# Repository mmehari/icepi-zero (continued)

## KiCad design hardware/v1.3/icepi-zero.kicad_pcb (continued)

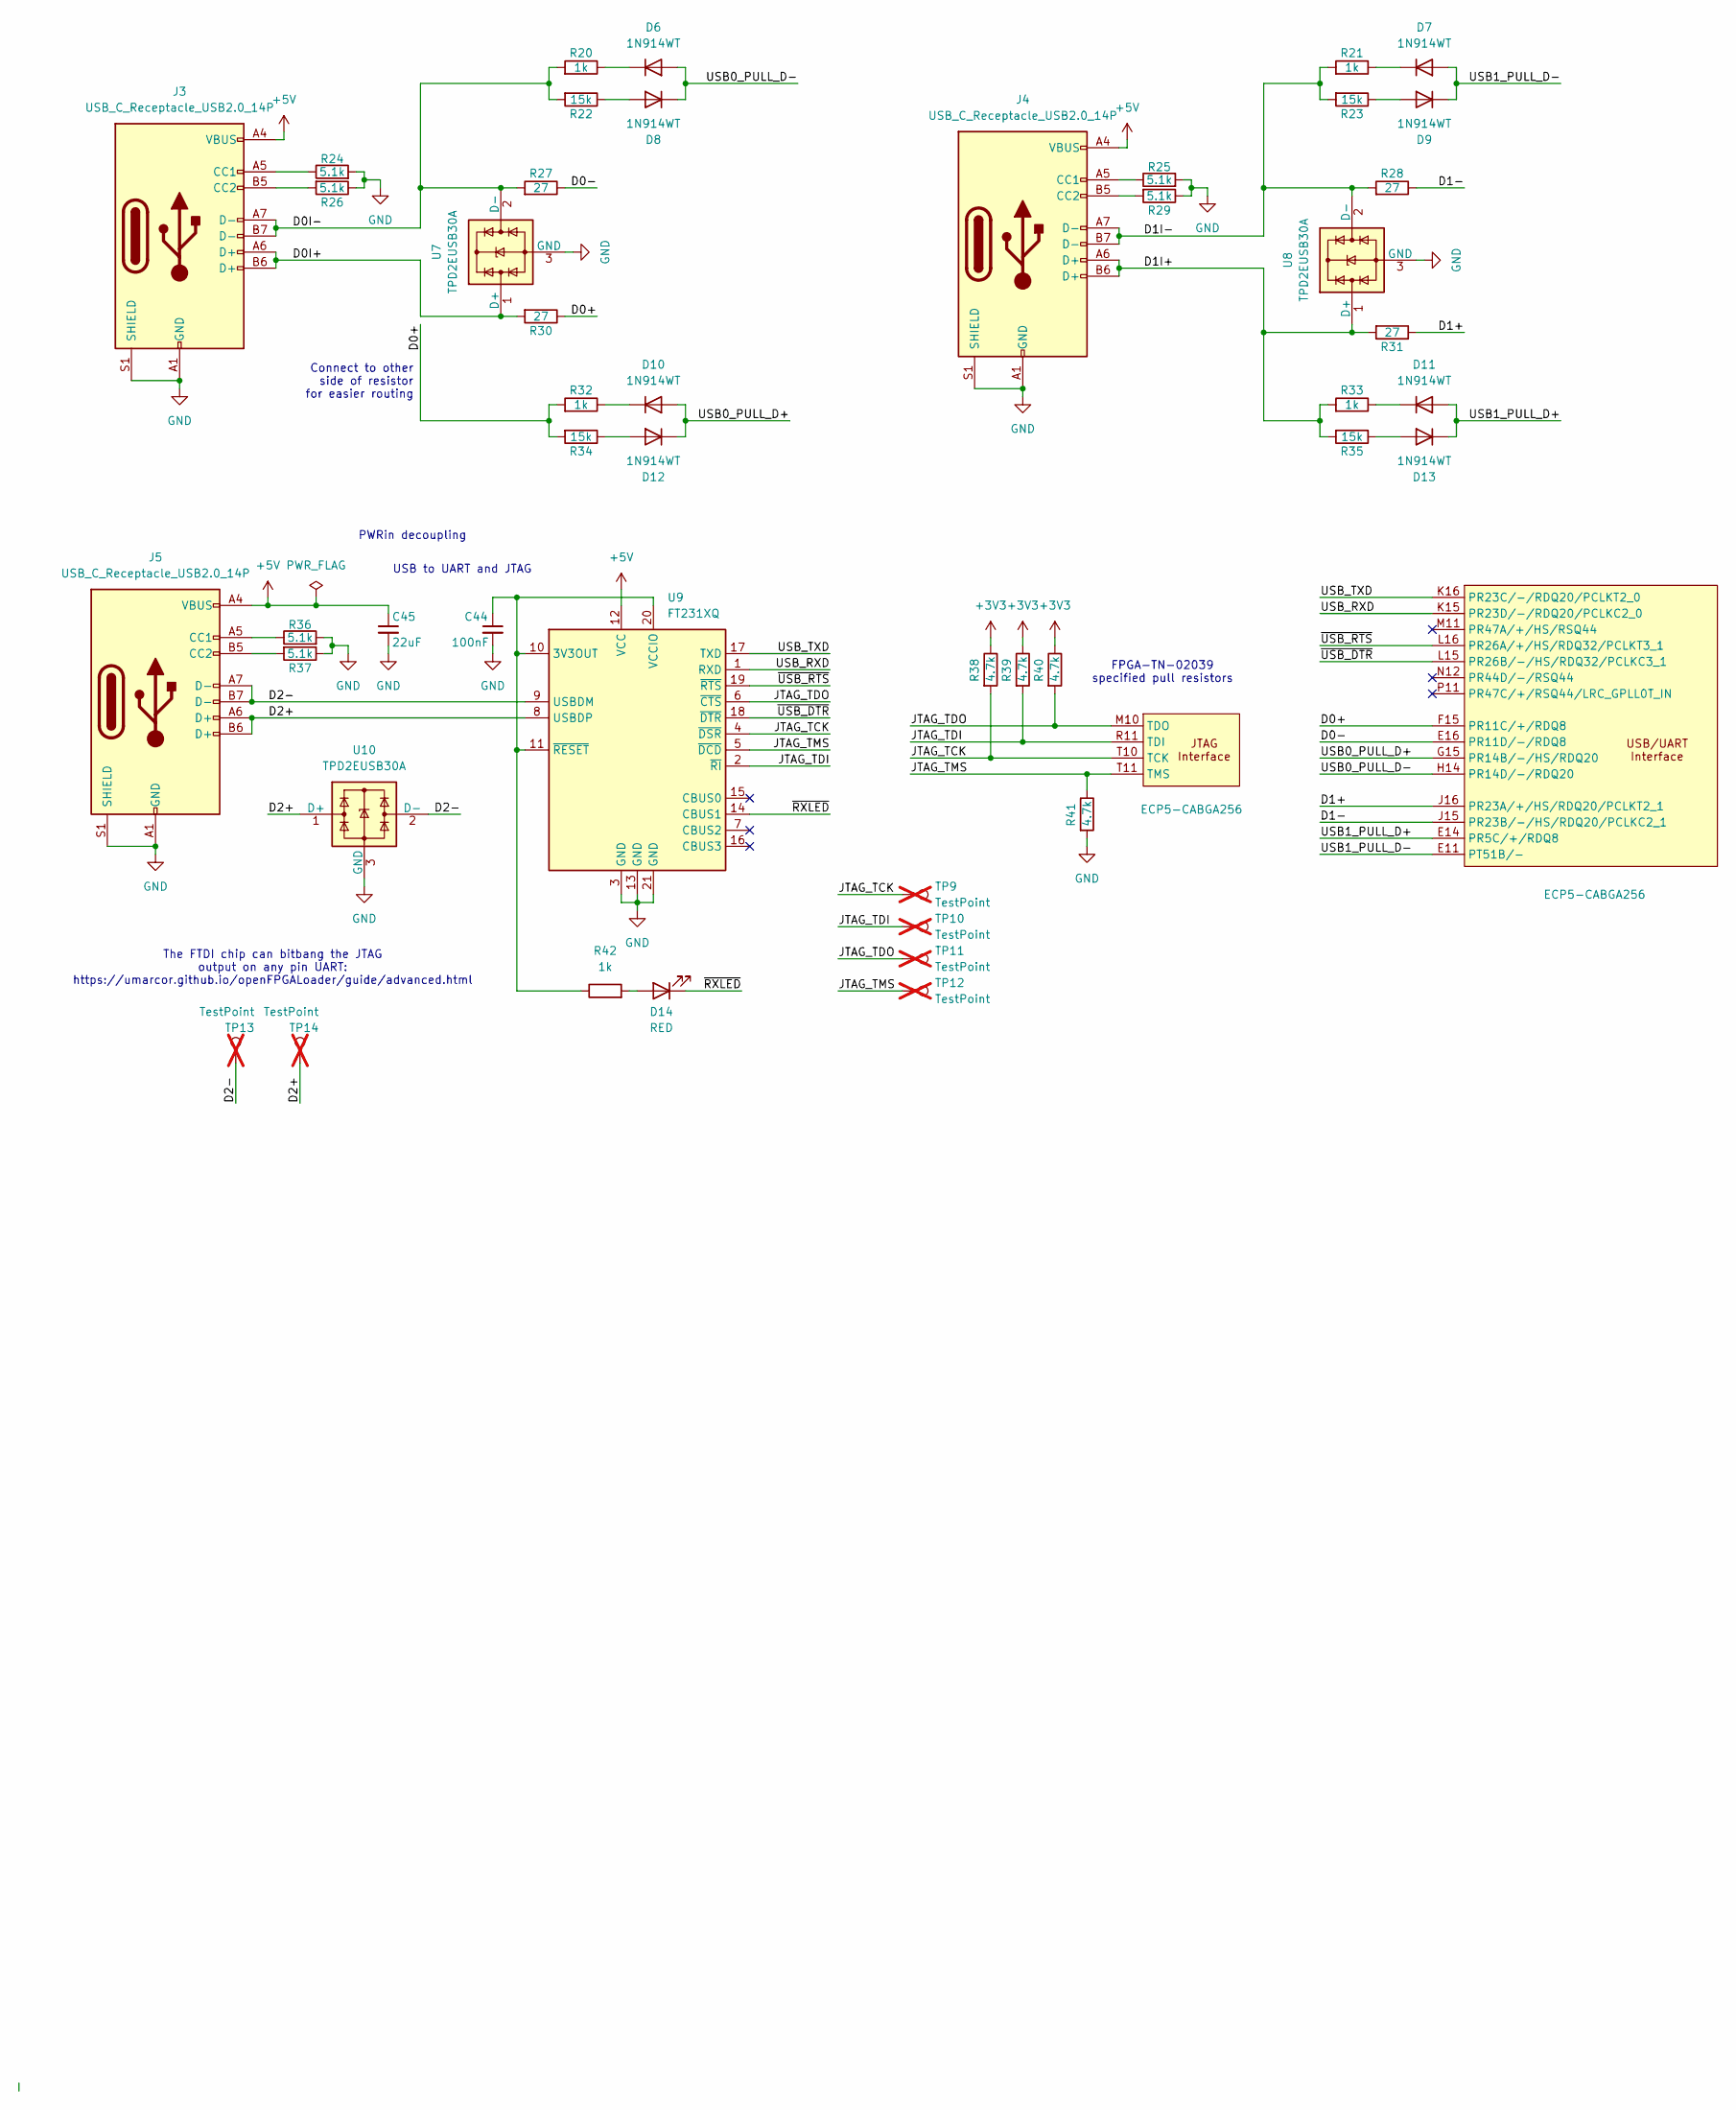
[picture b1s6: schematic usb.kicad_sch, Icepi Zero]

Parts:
C44: 100nF; C_0402_1005Metric; Manufactuer Part Number CL05B104KB54PNC; LCSC Part # C307331
C45: 22uF; C_0603_1608Metric; Manufactuer Part Number CL10A226MQ8NRNC; LCSC Part # C59461
D6, D7, D8, D9, D10, D11, D12, D13: 1N914WT; D_SOD-523; Manufactuer Part Number 1N914WT; LCSC Part # C2836064
D14: RED; LED_0603_1608Metric; Manufactuer Part Number KT-0603R; LCSC Part # C2286
J3, J4, J5: USB_C_Receptacle_USB2.0_14P; USB_C_Receptacle_GCT_USB4105-xx-A_16P_TopMnt_Horizontal; Manufactuer Part Number TYPE-C 16PIN 2MD(073); LCSC Part # C2765186
R20, R21, R32, R33, R42: 1k; R_0402_1005Metric; Manufactuer Part Number 0402WGF1001TCE; LCSC Part # C11702
R22, R23, R34, R35: 15k; R_0402_1005Metric; Manufactuer Part Number 0402WGF1502TCE; LCSC Part # C25756
R24, R25, R26, R29, R36, R37: 5.1k; R_0402_1005Metric; Manufactuer Part Number 0402WGF5101TCE; LCSC Part # C25905
R27, R28, R30, R31: 27; R_0201_0603Metric; Manufactuer Part Number 0201WMF270JTEE; LCSC Part # C473051
R38, R39, R40, R41: 4.7k; R_0402_1005Metric; Manufactuer Part Number 0402WGF4701TCE; LCSC Part # C25900
TP9, TP10, TP11, TP12: TestPoint; TestPoint_Pad_D1.0mm_Blank; not fitted
TP13, TP14: TestPoint; TestPoint_Pad_D2.0mm_Blank; not fitted
U1: ECP5-CABGA256; BGA-256_14.0x14.0mm_Layout16x16_P0.8mm_Ball0.45mm_Pad0.32mm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; Manufactuer Part Number LFE5U-25F-6BG256C; LCSC Part # C1521614
U7, U8, U10: TPD2EUSB30A; Texas_DRT-3; Manufactuer Part Number TPD2EUSB30ADRTR; LCSC Part # C3011197
U9: FT231XQ; QFN-20-1EP_4x4mm_P0.5mm_EP2.5x2.5mm; Manufactuer Part Number FT231XQ-R; LCSC Part # C132159

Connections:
+3V3: R38.1, R39.1, R40.1; also elsewhere on the board
+5V: C45.1, J3.A4 (VBUS), J3.A9 (VBUS), J3.B4 (VBUS), J3.B9 (VBUS), J4.A4 (VBUS), J4.A9 (VBUS), J4.B4 (VBUS), J4.B9 (VBUS), J5.A4 (VBUS), J5.A9 (VBUS), J5.B4 (VBUS), J5.B9 (VBUS), U9.12 (VCC); also elsewhere on the board
/DBG1: U1.C7 (PT27A/+/PCLKT0_1); also elsewhere on the board
/DBG2: U1.C8 (PT35A/+/PCLKT1_0); also elsewhere on the board
/GLOBAL_CLK: U1.M1 (PL26C/+/LDQ32/PCLKT6_0); also elsewhere on the board
/GPIO0: U1.G3 (PL14C/+/LDQ20/VREF1_7); also elsewhere on the board
/GPIO1: U1.K3 (PL20D/-/LDQS20); also elsewhere on the board
/GPIO2: U1.T2 (PL38D/-/LDQ44); also elsewhere on the board
/GPIO3: U1.R2 (PL38C/+/LDQ44); also elsewhere on the board
/GPIO4: U1.R1 (PL35B/-/HS/LDQ32/VREF1_6); also elsewhere on the board
/GPIO5: U1.E1 (PL11D/-/LDQ8); also elsewhere on the board
/GPIO6: U1.F3 (PL5D/-/LDQ8); also elsewhere on the board
/GPIO7: U1.G1 (PL20A/+/HS/LDQS20/GR_PCLK7_1); also elsewhere on the board
/GPIO8: U1.H2 (PL20C/+/LDQS20/GR_PCLK7_0); also elsewhere on the board
/GPIO9: U1.J1 (PL23A/+/HS/LDQ20/PCLKT7); also elsewhere on the board
/GPIO10: U1.L2 (PL26B/-/HS/LDQ32/PCLKC6_1); also elsewhere on the board
/GPIO11: U1.G2 (PL14B/-/HS/LDQ20); also elsewhere on the board
/GPIO12: U1.J3 (PL20B/-/HS/LDQSN20); also elsewhere on the board
/GPIO13: U1.E3 (PL5C/+/LDQ8); also elsewhere on the board
/GPIO14: U1.P1 (PL35A/+/HS/LDQ32); also elsewhere on the board
/GPIO15: U1.N1 (PL32A/+/HS/LDQS32); also elsewhere on the board
/GPIO16: U1.H3 (PL14D/-/lDQ20); also elsewhere on the board
/GPIO17: U1.R3 (PL41B/-/HS/LDQ44); also elsewhere on the board
/GPIO18: U1.N4 (PL38A/+/HS/LDQ44); also elsewhere on the board
/GPIO19: U1.E4 (PT9A/+); also elsewhere on the board
/GPIO20: U1.F1 (PL14A/+/HS/LDQ20); also elsewhere on the board
/GPIO21: U1.F2 (PL11C/+/LDQ8); also elsewhere on the board
/GPIO22: U1.P2 (PL32B/-/HS/LDQSN32); also elsewhere on the board
/GPIO23: U1.M2 (PL26D/-/LDQ32/PCLK6_0); also elsewhere on the board
/GPIO24: U1.L1 (PL26A/+/HS/LDQ32/PCLKT6_1); also elsewhere on the board
/GPIO25: U1.J2 (PL23B/-/HS/LDQ20/PCLKC7_1); also elsewhere on the board
/GPIO26: U1.D4 (PT9B/-); also elsewhere on the board
/GPIO27: U1.P3 (PL38B/-/HS/LDQ44); also elsewhere on the board
/LED0: U1.E13 (PT62B/-); also elsewhere on the board
/LED1: U1.D14 (PR2D/-/RDQ8); also elsewhere on the board
/LED2: U1.E12 (PT58B/-); also elsewhere on the board
/LED3: U1.C13 (PT60B/-); also elsewhere on the board
/LED4: U1.D13 (PT62A/+); also elsewhere on the board
/SW0: U1.C4 (PT11A/+); also elsewhere on the board
/SW1: U1.C5 (PT15A/+); also elsewhere on the board
/USB/D0+: R30.1, R32.2, R34.2, U1.F15 (PR11C/+/RDQ8)
/USB/D0-: R27.1, U1.E16 (PR11D/-/RDQ8)
/USB/D0I+: J3.A6 (D+), J3.B6 (D+), R30.2, U7.1 (D+)
/USB/D0I-: J3.A7 (D-), J3.B7 (D-), R20.2, R22.2, R27.2, U7.2 (D-)
/USB/D1+: R31.1, U1.J16 (PR23A/+/HS/RDQ20/PCLKT2_1)
/USB/D1-: R28.1, U1.J15 (PR23B/-/HS/RDQ20/PCLKC2_1)
/USB/D1I+: J4.A6 (D+), J4.B6 (D+), R31.2, R33.2, R35.2, U8.1 (D+)
/USB/D1I-: J4.A7 (D-), J4.B7 (D-), R21.2, R23.2, R28.2, U8.2 (D-)
/USB/D2+: J5.A6 (D+), J5.B6 (D+), TP14.1, U9.8 (USBDP), U10.1 (D+)
/USB/D2-: J5.A7 (D-), J5.B7 (D-), TP13.1, U9.9 (USBDM), U10.2 (D-)
/USB/JTAG_TCK: R38.2, TP9.1, U1.T10 (TCK), U9.4 (~DSR)
/USB/JTAG_TDI: R39.2, TP10.1, U1.R11 (TDI), U9.2 (~RI)
/USB/JTAG_TDO: R40.2, TP11.1, U1.M10 (TDO), U9.6 (~CTS)
/USB/JTAG_TMS: R41.1, TP12.1, U1.T11 (TMS), U9.5 (~DCD)
/USB/USB0_PULL_D+: D10.2 (A), D12.1 (K), U1.G15 (PR14B/-/HS/RDQ20)
/USB/USB0_PULL_D-: D6.2 (A), D8.1 (K), U1.H14 (PR14D/-/RDQ20)
/USB/USB1_PULL_D+: D11.2 (A), D13.1 (K), U1.E14 (PR5C/+/RDQ8)
/USB/USB1_PULL_D-: D7.2 (A), D9.1 (K), U1.E11 (PT51B/-)
/USB/USB_RXD: U1.K15 (PR23D/-/RDQ20/PCLKC2_0), U9.1 (RXD)
/USB/USB_TXD: U1.K16 (PR23C/-/RDQ20/PCLKT2_0), U9.17 (TXD)
/USB/~RXLED: D14.1 (K), U9.14 (CBUS1)
/USB/~USB_DTR: U1.L15 (PR26B/-/HS/RDQ32/PCLKC3_1), U9.18 (~DTR)
/USB/~USB_RTS: U1.L16 (PR26A/+/HS/RDQ32/PCLKT3_1), U9.19 (~RTS)
GND: C44.2, C45.2, J3.A1 (GND), J3.A12 (GND), J3.B1 (GND), J3.B12 (GND), J3.S1 (SHIELD), J4.A1 (GND), J4.A12 (GND), J4.B1 (GND), J4.B12 (GND), J4.S1 (SHIELD), J5.A1 (GND), J5.A12 (GND), J5.B1 (GND), J5.B12 (GND), J5.S1 (SHIELD), R24.2, R25.2, R26.1, R29.1, R36.2, R37.1, R41.2, U7.3 (GND), U8.3 (GND), U9.3 (GND), U9.13 (GND), U9.21 (GND), U10.3 (GND); also elsewhere on the board
unnamed: D6.1 (K), R20.1
unnamed: D7.1 (K), R21.1
unnamed: D8.2 (A), R22.1
unnamed: D9.2 (A), R23.1
unnamed: D10.1 (K), R32.1
unnamed: D11.1 (K), R33.1
unnamed: D12.2 (A), R34.1
unnamed: D13.2 (A), R35.1
unnamed: D14.2 (A), R42.2
unnamed: J3.A5 (CC1), R24.1
unnamed: J3.B5 (CC2), R26.2
unnamed: J4.A5 (CC1), R25.1
unnamed: J4.B5 (CC2), R29.2
unnamed: J5.A5 (CC1), R36.1
unnamed: J5.B5 (CC2), R37.2
unnamed: C44.1, R42.1, U9.10 (3V3OUT), U9.11 (~RESET), U9.20 (VCCIO)

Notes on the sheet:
PWRin decoupling
FPGA-TN-02039 specified pull resistors
USB to UART and JTAG
The FTDI chip can bitbang the JTAG output on any pin UART: https://umarcor.github.io/openFPGALoader/guide/advanced.html
Connect to other side of resistor for easier routing

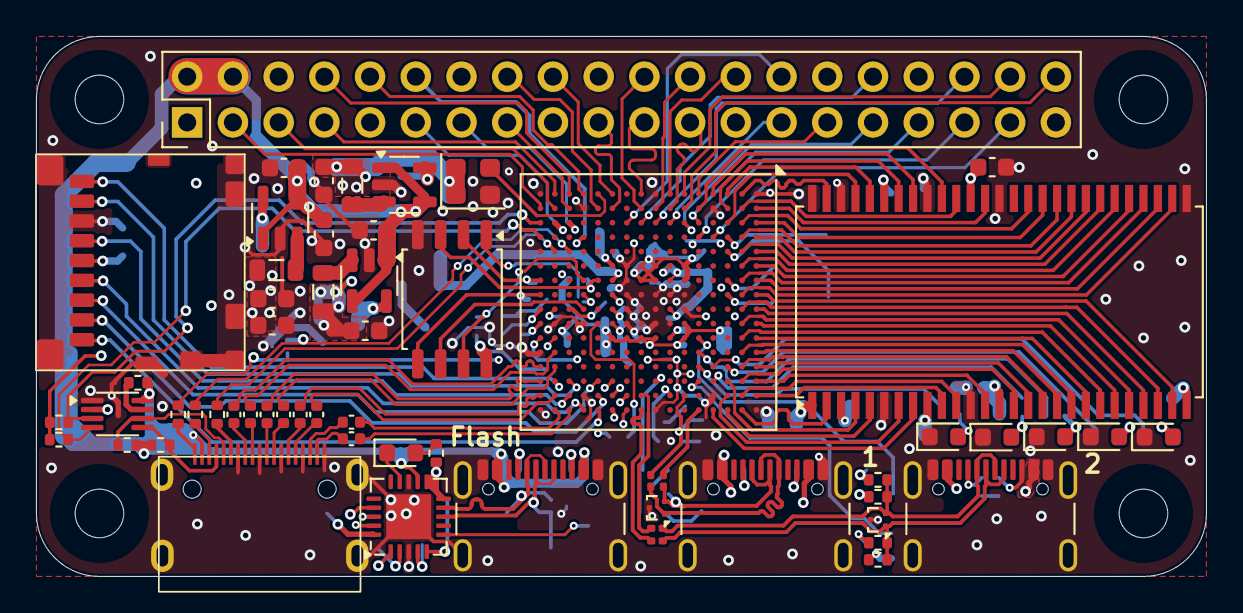
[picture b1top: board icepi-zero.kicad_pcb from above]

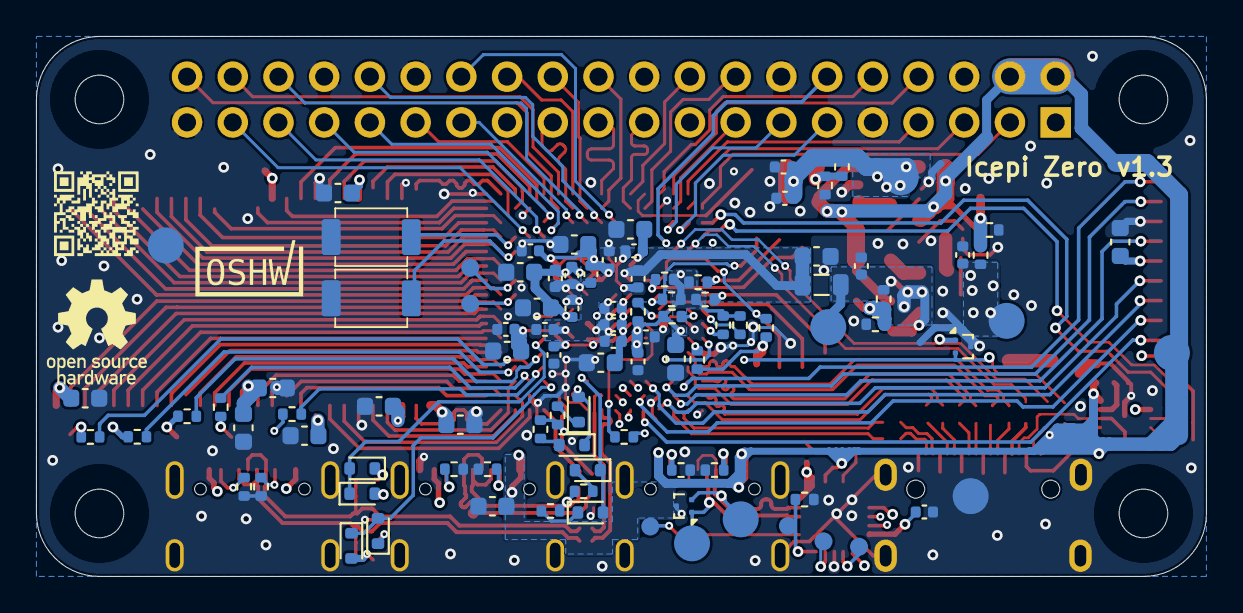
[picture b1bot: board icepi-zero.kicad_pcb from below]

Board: 4 copper layers, 65.0 x 30.0 mm, 162 parts (99 on the bottom side), 176 nets.

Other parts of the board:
C1: 100nF; C_0402_1005Metric
D1, D2, D3, D4, D5: WHITE; LED_0603_1608Metric
H1, H2, H3, H4: MountingHole; MountingHole_2.7mm_M2.5
J1: Conn_02x20_Counter_Clockwise; PinHeader_2x20_P2.54mm_Vertical
LOGO1: OSHW-Certification-Mark-Logo_6x3mm_SilkScreen
R1, R2, R3, R4, R5: 1k; R_0402_1005Metric
SW1, SW2: SW_Push; switch_button_TS-1088-AR02016
TP1, TP2, TP3, TP4, TP5, TP6: TestPoint; TestPoint_Pad_D2.0mm_Blank
TP7, TP8: TestPoint; TestPoint_Pad_D1.0mm_Blank
Y1: SG-8018CG 50.000000MHz; Oscillator_SMD_SiT_PQFN-4Pin_2.5x2.0mm

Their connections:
+1V1: TP6.1; also elsewhere on the board
+2V5: TP5.1; also elsewhere on the board
+3V3: C1.1, J1.1, J1.17, TP4.1, Y1.1 (OE), Y1.4 (Vdd); also elsewhere on the board
+5V: J1.2, J1.4, TP3.1; also elsewhere on the board
/DBG1: TP8.1; also elsewhere on the board
/DBG2: TP7.1; also elsewhere on the board
/GLOBAL_CLK: Y1.3 (OUT); also elsewhere on the board
/GPIO0: J1.27; also elsewhere on the board
/GPIO1: J1.28; also elsewhere on the board
/GPIO2: J1.3; also elsewhere on the board
/GPIO3: J1.5; also elsewhere on the board
/GPIO4: J1.7; also elsewhere on the board
/GPIO5: J1.29; also elsewhere on the board
/GPIO6: J1.31; also elsewhere on the board
/GPIO7: J1.26; also elsewhere on the board
/GPIO8: J1.24; also elsewhere on the board
/GPIO9: J1.21; also elsewhere on the board
/GPIO10: J1.19; also elsewhere on the board
/GPIO11: J1.23; also elsewhere on the board
/GPIO12: J1.32; also elsewhere on the board
/GPIO13: J1.33; also elsewhere on the board
/GPIO14: J1.8; also elsewhere on the board
/GPIO15: J1.10; also elsewhere on the board
/GPIO16: J1.36; also elsewhere on the board
/GPIO17: J1.11; also elsewhere on the board
/GPIO18: J1.12; also elsewhere on the board
/GPIO19: J1.35; also elsewhere on the board
/GPIO20: J1.38; also elsewhere on the board
/GPIO21: J1.40; also elsewhere on the board
/GPIO22: J1.15; also elsewhere on the board
/GPIO23: J1.16; also elsewhere on the board
/GPIO24: J1.18; also elsewhere on the board
/GPIO25: J1.22; also elsewhere on the board
/GPIO26: J1.37; also elsewhere on the board
/GPIO27: J1.13; also elsewhere on the board
/LED0: R1.1; also elsewhere on the board
/LED1: R2.1; also elsewhere on the board
/LED2: R3.1; also elsewhere on the board
/LED3: R4.1; also elsewhere on the board
/LED4: R5.1; also elsewhere on the board
/SW0: SW1.1; also elsewhere on the board
/SW1: SW2.1; also elsewhere on the board
GND: C1.2, D1.1 (K), D2.1 (K), D3.1 (K), D4.1 (K), D5.1 (K), J1.6, J1.9, J1.14, J1.20, J1.25, J1.30, J1.34, J1.39, SW1.2, SW2.2, TP1.1, TP2.1, Y1.2 (GND); also elsewhere on the board
unnamed: D1.2 (A), R1.2
unnamed: D2.2 (A), R2.2
unnamed: D3.2 (A), R3.2
unnamed: D4.2 (A), R4.2
unnamed: D5.2 (A), R5.2

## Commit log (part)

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2026-01-11 Added JTAG demo
2026-01-14 Add instructions for Diamond IDE
2026-01-25 Upload documentation screenshots
2026-02-01 Replace not accecable contact
2026-02-25 Remove weird lock on a trace
2026-03-19 Add a filter for non-human contributors
2026-04-03 Add acknowledgments
2026-04-03 Add link to nes port
2026-04-03 Updated OpenOCD config for icepi-zero to restore UART mode on exit.
2026-04-03 Added 3D printable case.
2026-04-03 Add note about screw sizes
2026-04-04 Add video
2026-04-23 Add link
2026-05-13 README typos
2026-05-13 switch was still bouncing
2026-05-24 Add link to @danodus's ECP5 Audio + Video Transmitter
2026-05-26 Educational benefits :p
2026-06-17 Added a few links
2026-06-27 QOL improvements on v1.3 PCB
